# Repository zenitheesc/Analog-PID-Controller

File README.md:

<h1 align="center" style="color:white; background-color:black">Analog PID Controller</h1>
<h4 align="center">
The project was developed in three parts. The first was a simetric supply to 6V at -6V, that was responsable to supply the requires voltages to second part, the PID controler. The PID controller was developed using operational amplifiers in derivatived and integral configuration The tird one was a motor velocity and position sensor, developed using fotodiodes like an encoder.</h4>

<p align="center">

</p>

---

<p align="center">

</p>
<p align = "center">
<a href="zenith.eesc@gmail.com">zenith.eesc@gmail.com</a>
</p>

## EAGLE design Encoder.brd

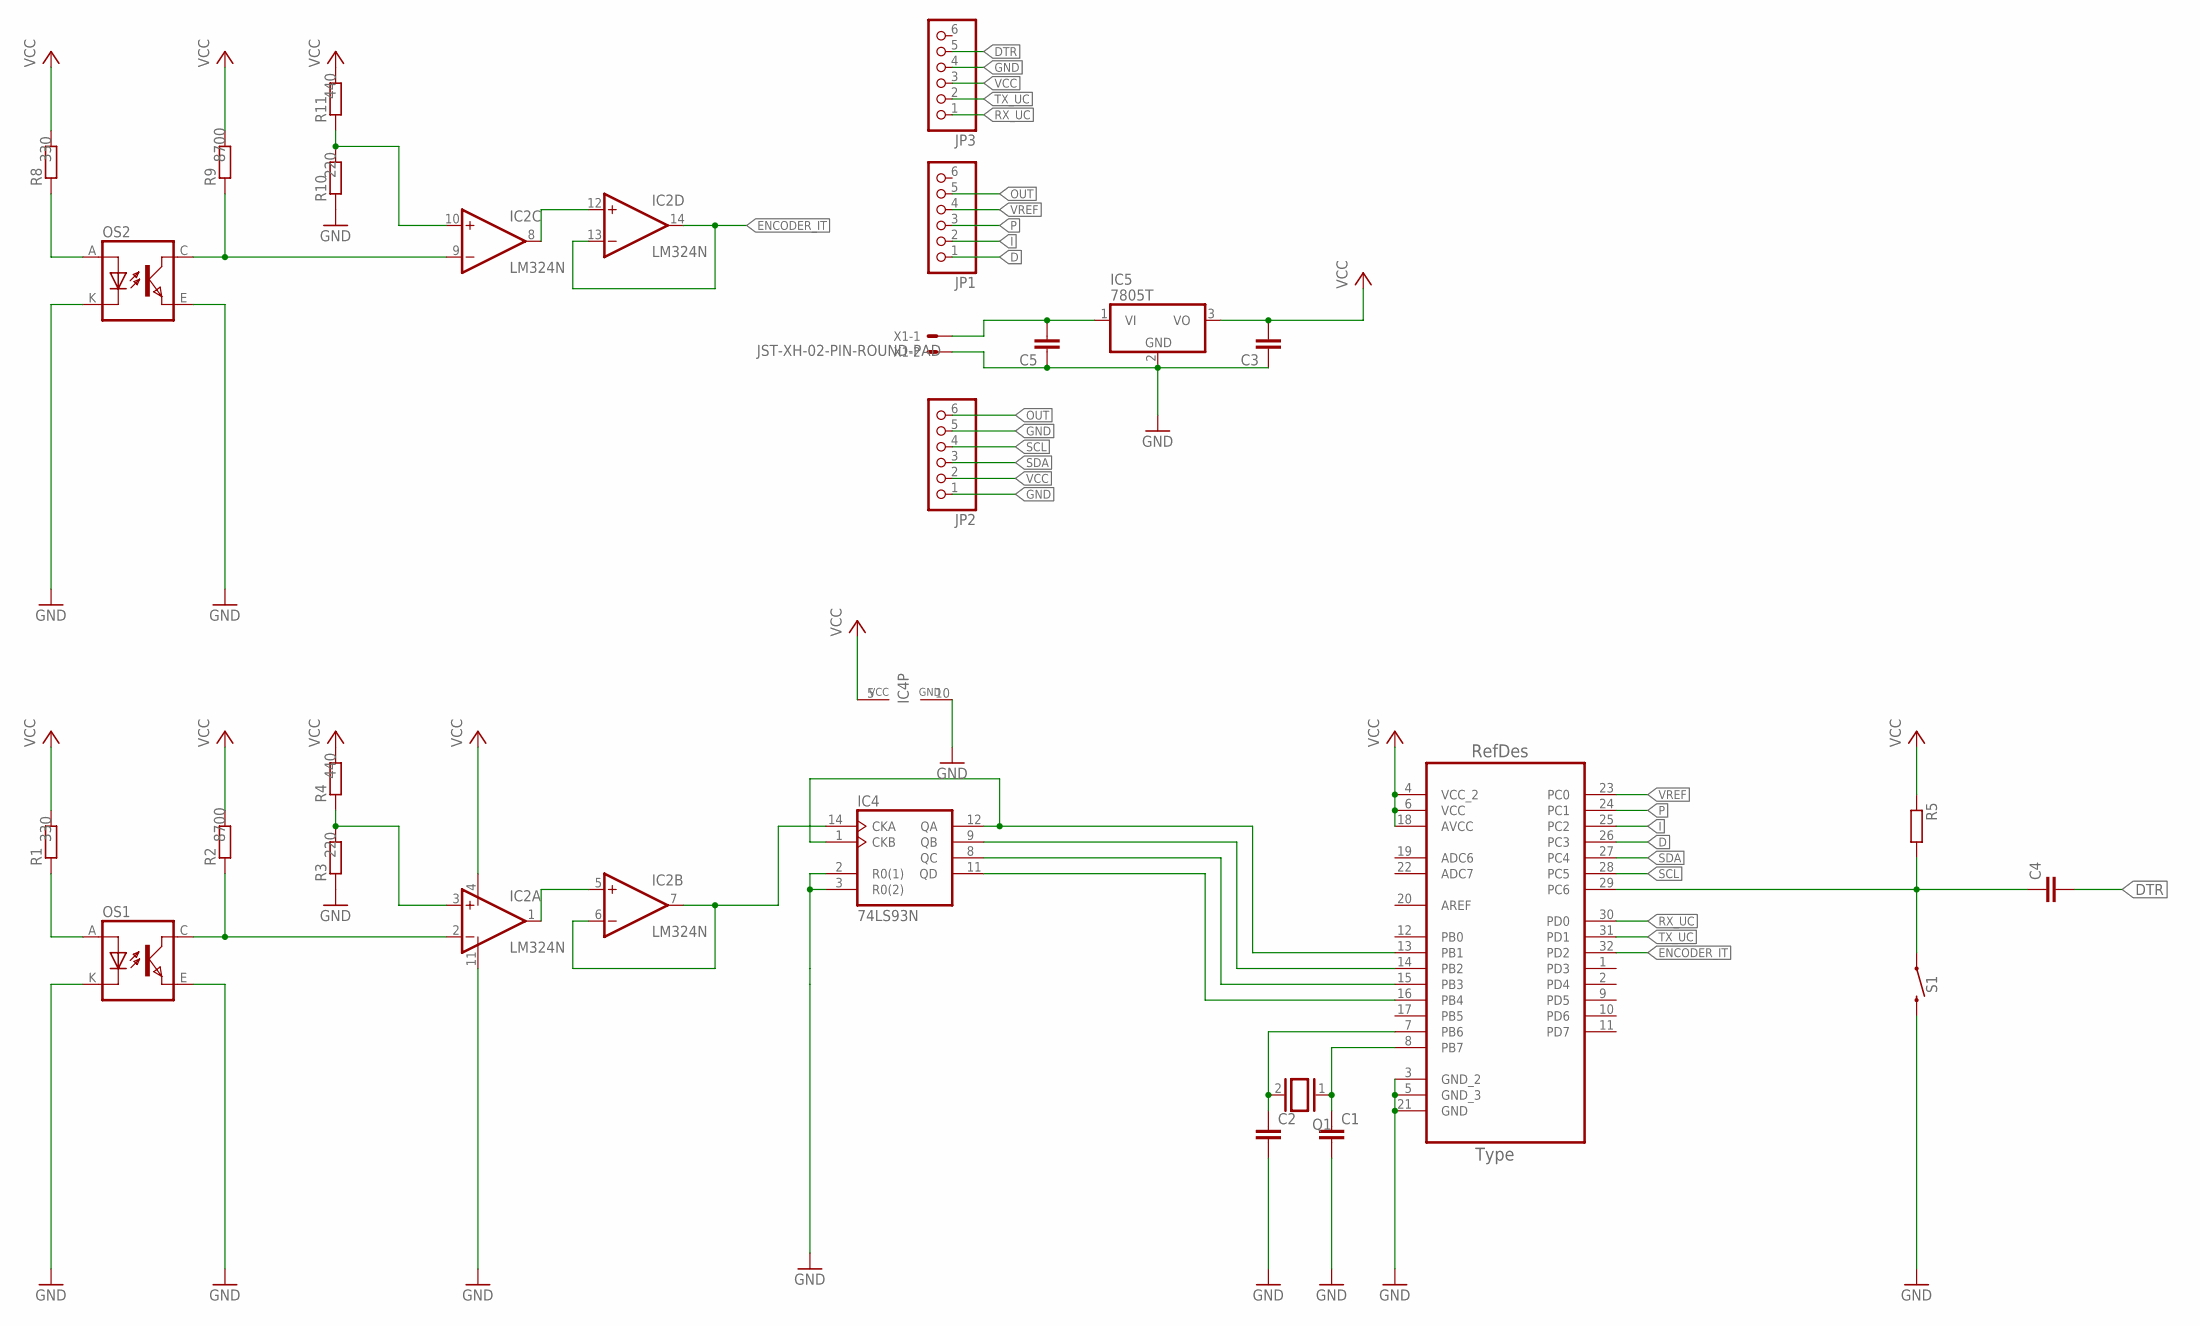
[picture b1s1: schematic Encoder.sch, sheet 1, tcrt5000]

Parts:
C1, C2, C3, C4, C5: C-EUC1206; C1206
IC2: LM324N; DIL14
IC4: 74LS93N; DIL14
IC5: 7805T; TO220H
JP1, JP2, JP3: PINHD-1X6; 1X06
OS1, OS2: TCRT5000
Q1: XTAL/S; QS
R1, R2, R3, R4, R5, R8, R9, R10, R11: R-EU_M1206; M1206
S1: MOMENTARY-SWITCH-SPST-PTH-6.0MM; TACTILE_SWITCH_PTH_6.0MM
U1: ATMEGA328P-AU; QFP80P900X900X120-32N
X1: JST-XH-02-PIN-ROUND-PAD; JST-XH-02-PACKAGE-ROUND-PAD

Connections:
D: JP1.1, U1.26 (PC3)
DTR: C4.2, JP3.5
ENCODER_IT: IC2.13 (-IN), IC2.14 (OUT), U1.32 (PD2)
GND: C1.2, C2.2, C3.1, C5.1, IC2.11 (V-), IC4.2 (R0(1)), IC4.3 (R0(2)), IC4.10 (GND), IC5.2 (GND), JP2.1, JP2.5, JP3.4, OS1.E (EMITTER), OS1.K (CATHODE), OS2.E (EMITTER), OS2.K (CATHODE), R3.1, R10.1, S1.3 (2), U1.3 (GND_2), U1.5 (GND_3), U1.21 (GND), X1.2
I: JP1.2, U1.25 (PC2)
unnamed: OS1.A (ANODE), R1.1
unnamed: IC2.2 (-IN), OS1.C (COLLECTOR), R2.1
unnamed: IC2.3 (+IN), R3.2, R4.1
unnamed: IC2.1 (OUT), IC2.5 (+IN)
unnamed: C1.1, Q1.1, U1.8 (PB7)
unnamed: C5.2, IC5.1 (VI), X1.1
unnamed: C2.1, Q1.2, U1.7 (PB6)
unnamed: C4.1, R5.2, S1.1, U1.29 (PC6)
unnamed: IC2.6 (-IN), IC2.7 (OUT), IC4.14 (CKA)
unnamed: IC4.1 (CKB), IC4.12 (QA), U1.13 (PB1)
unnamed: IC2.8 (OUT), IC2.12 (+IN)
unnamed: IC4.9 (QB), U1.14 (PB2)
unnamed: OS2.A (ANODE), R8.1
unnamed: IC2.9 (-IN), OS2.C (COLLECTOR), R9.1
unnamed: IC2.10 (+IN), R10.2, R11.1
unnamed: IC4.8 (QC), U1.15 (PB3)
unnamed: IC4.11 (QD), U1.16 (PB4)
OUT: JP1.5, JP2.6
P: JP1.3, U1.24 (PC1)
RX_UC: JP3.1, U1.30 (PD0)
SCL: JP2.4, U1.28 (PC5)
SDA: JP2.3, U1.27 (PC4)
TX_UC: JP3.2, U1.31 (PD1)
VCC: C3.2, IC2.4 (V+), IC4.5 (VCC), IC5.3 (VO), JP2.2, JP3.3, R1.2, R2.2, R4.2, R5.1, R8.2, R9.2, R11.2, U1.4 (VCC_2), U1.6 (VCC), U1.18 (AVCC)
VREF: JP1.4, U1.23 (PC0)

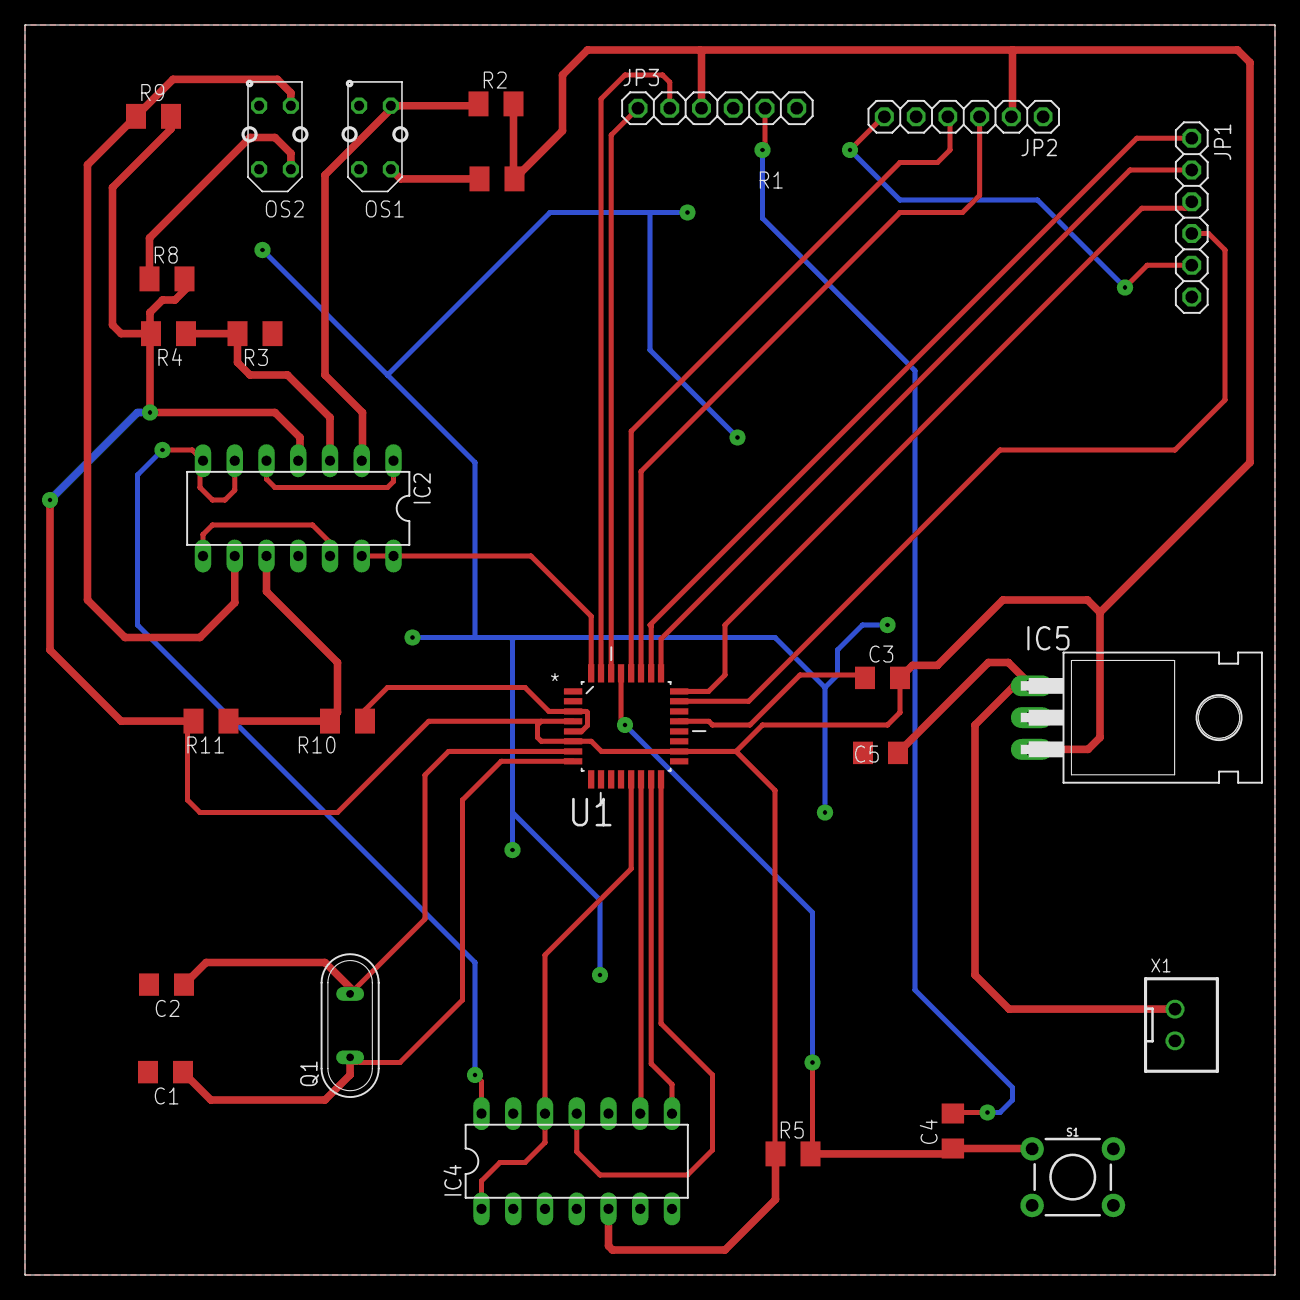
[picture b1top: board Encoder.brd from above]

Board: 2 copper layers, 100.0 x 100.0 mm, 26 parts (0 on the bottom side), 30 nets.

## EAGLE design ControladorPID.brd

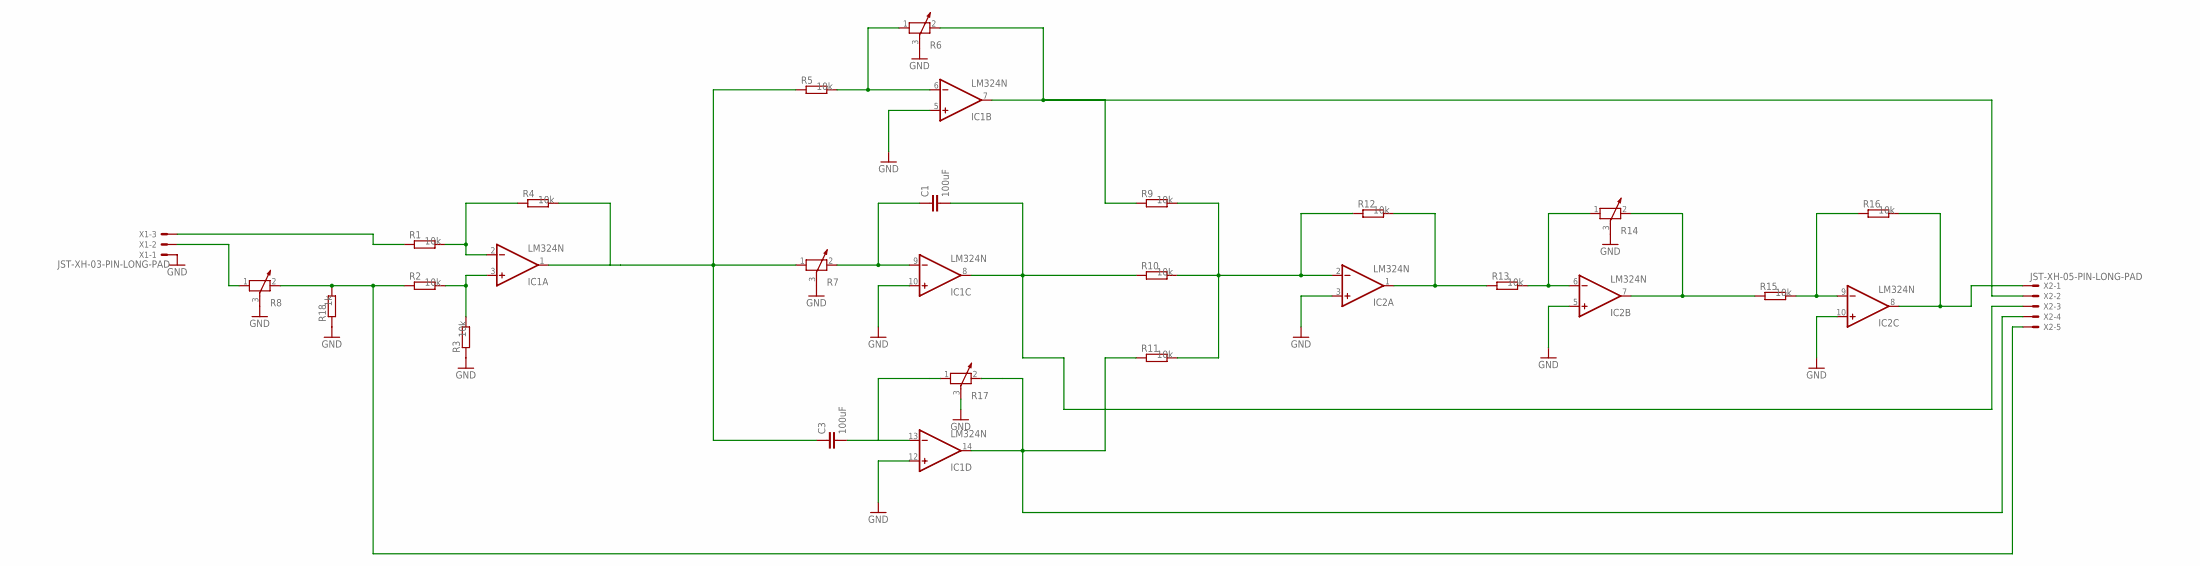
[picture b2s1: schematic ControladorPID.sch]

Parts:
C1, C3: 100uF; C2.5-3
IC1, IC2: LM324N; DIL14
R1, R2, R3, R4, R5, R9, R10, R11, R12, R13, R15, R16, R18: R-EU_M1206; M1206
R6, R7, R8, R14, R17: POTENTIOMETER_PT-10; PT-10
X1: JST-XH-03-PIN-LONG-PAD; JST-XH-03-PACKAGE-LONG-PAD
X2: JST-XH-05-PIN-LONG-PAD; JST-XH-05-PACKAGE-LONG-PAD

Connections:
GND: IC1.5 (+IN), IC1.10 (+IN), IC1.12 (+IN), IC2.3 (+IN), IC2.5 (+IN), IC2.10 (+IN), R3.1, R6.3, R7.3, R8.3, R14.3, R17.3, R18.1, X1.1
unnamed: IC1.2 (-IN), R1.2, R4.1
unnamed: IC1.3 (+IN), R2.2, R3.2
unnamed: C3.1, IC1.1 (OUT), R4.2, R5.1, R7.1
unnamed: C1.2, IC1.8 (OUT), R10.1, X2.3
unnamed: IC1.6 (-IN), R5.2, R6.1
unnamed: R1.1, X1.3
unnamed: C1.1, IC1.9 (-IN), R7.2
unnamed: C3.2, IC1.13 (-IN)
unnamed: IC1.14 (OUT), R11.1, R17.2, X2.4
unnamed: IC2.6 (-IN), R13.2, R14.1
unnamed: IC2.2 (-IN), R9.2, R10.2, R11.2, R12.1
unnamed: IC2.1 (OUT), R12.2, R13.1
unnamed: IC2.7 (OUT), R14.2, R15.1
unnamed: IC2.9 (-IN), R15.2, R16.1
unnamed: IC2.8 (OUT), R16.2, X2.1
unnamed: R2.1, R8.2, R18.2, X2.5
unnamed: R8.1, X1.2
unnamed: IC1.7 (OUT), R6.2, R9.1, X2.2
V+: IC1.4 (V+), IC2.4 (V+)
V-: IC1.11 (V-), IC2.11 (V-)

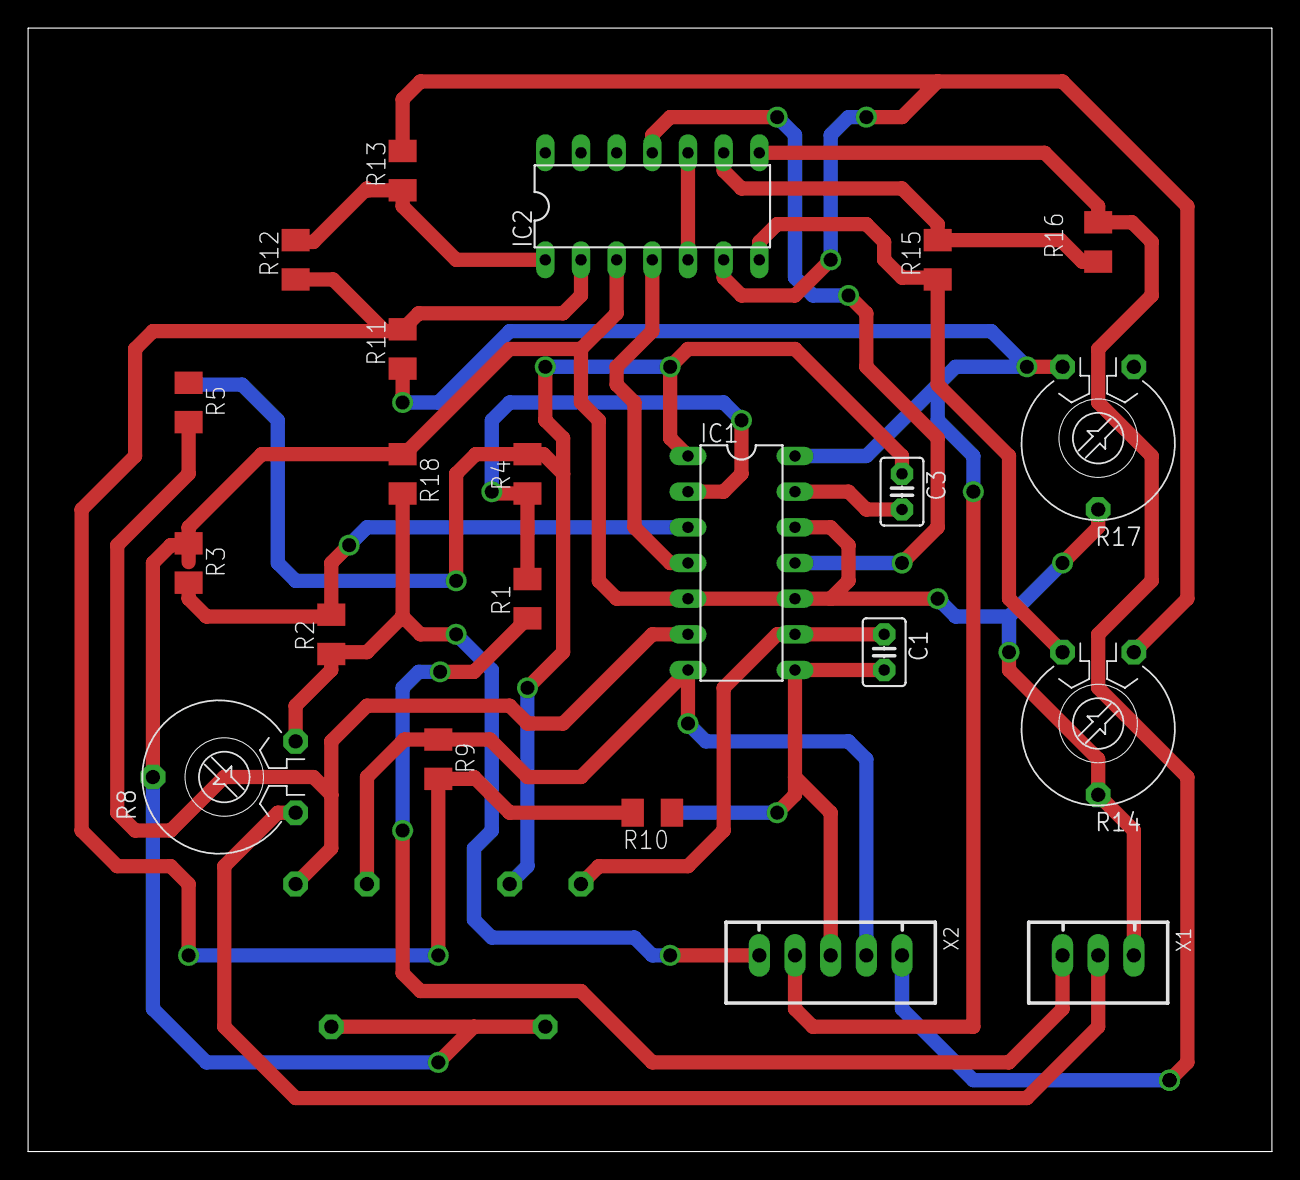
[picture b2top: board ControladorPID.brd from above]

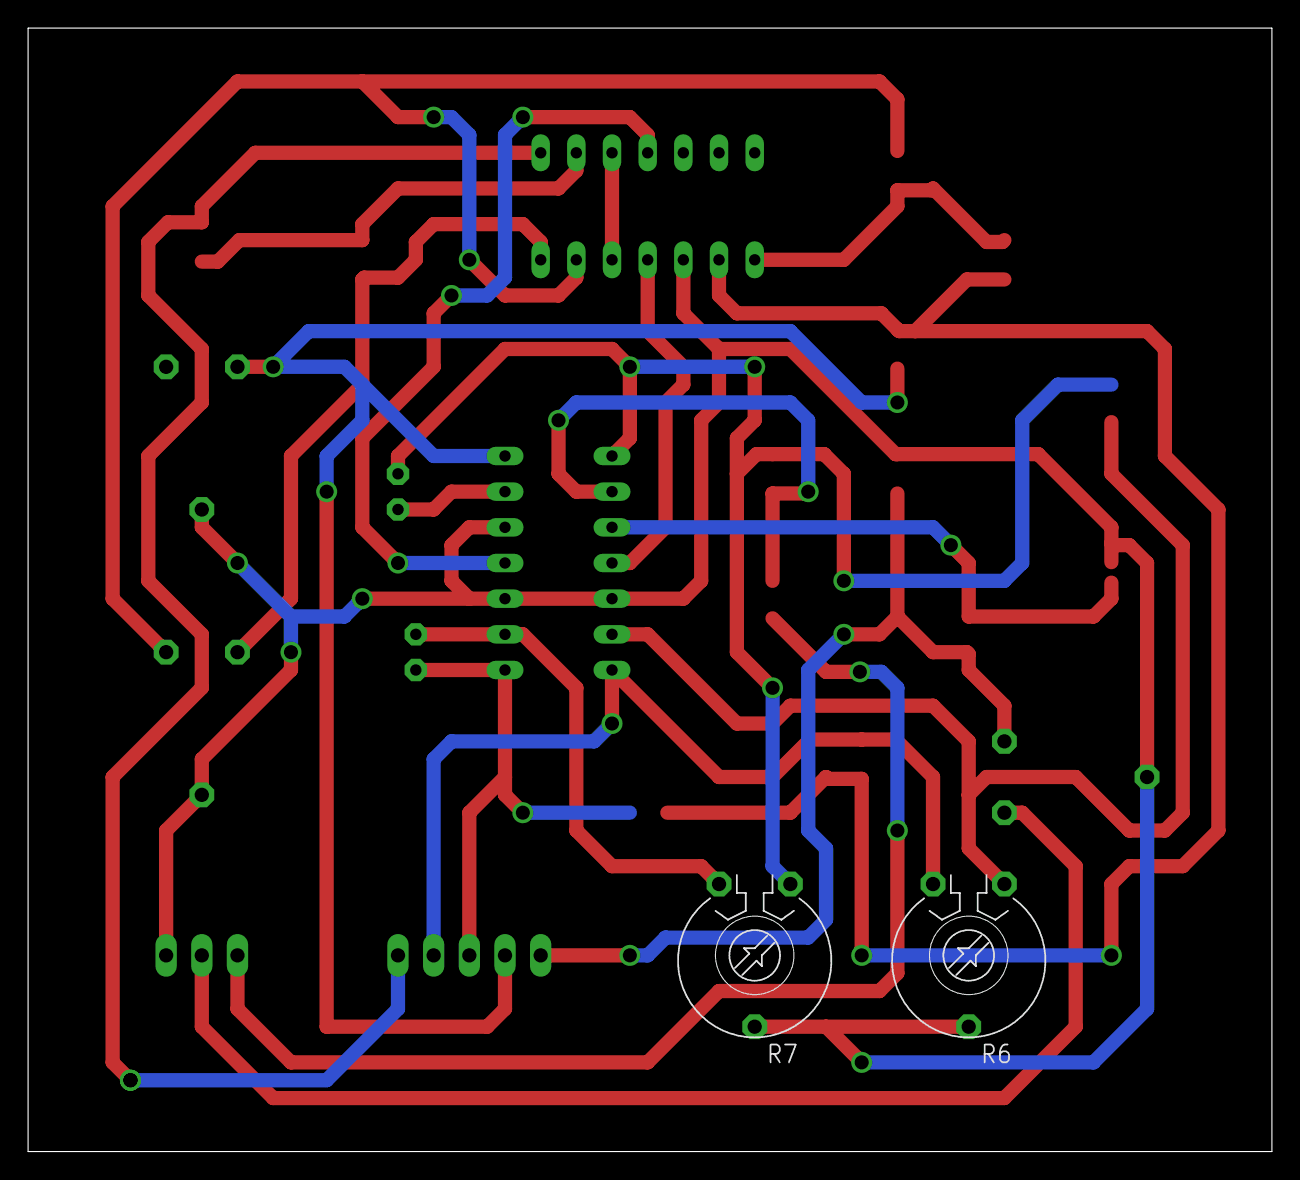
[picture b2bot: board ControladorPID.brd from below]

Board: 2 copper layers, 88.6 x 80.0 mm, 24 parts (2 on the bottom side), 21 nets.

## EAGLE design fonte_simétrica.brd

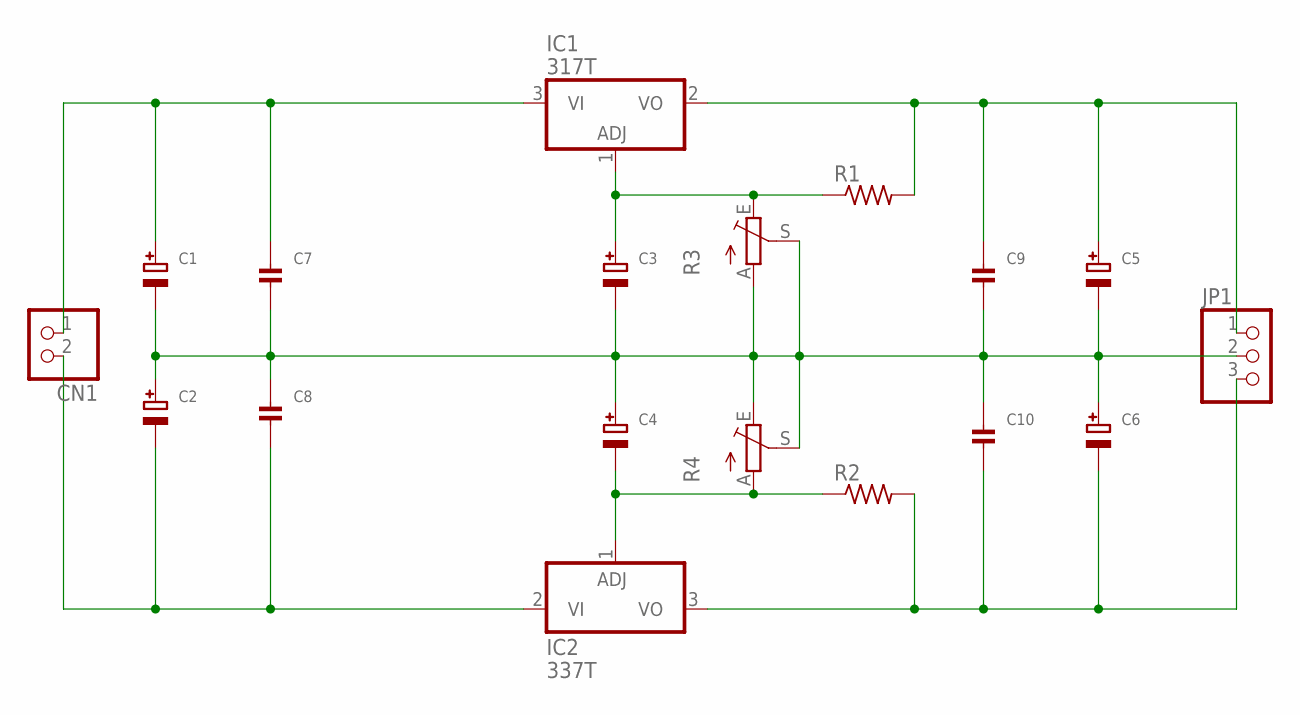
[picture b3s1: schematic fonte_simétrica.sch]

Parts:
C1, C2: CAP_ELECTROLYTICPTH_3.5MMGRID_10MMDIA; CELEC_3.5MM_10MM
C3, C4, C5, C6: CAP_ELECTROLYTICPTH_3.5MMGRID_8MMDIA; CELEC_3.5MM_8MM
C7, C8, C9, C10: CAP_CERAMIC0402; 0402
CN1: JST_2PIN-SMT; JST-PH-2-SMT
IC1: 317T; TO220H
IC2: 337T; TO220H
JP1: PINHD-1X3; 1X03
R1, R2: R-US_0204/7; 0204/7
R3, R4: TRIM_1234-S64YW; S64YW

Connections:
unnamed: C1.+, C7.1, CN1.1 (2), IC1.3 (VI)
unnamed: C1.-, C2.+, C3.-, C4.+, C5.-, C6.+, C7.2, C8.1, C9.2, C10.1, JP1.2, R3.A, R3.S, R4.E, R4.S
unnamed: C6.-, C10.2, IC2.3 (VO), JP1.3, R2.2
unnamed: C2.-, C8.2, CN1.2 (1), IC2.2 (VI)
unnamed: C3.+, IC1.1 (ADJ), R1.1, R3.E
unnamed: C5.+, C9.1, IC1.2 (VO), JP1.1, R1.2
unnamed: C4.-, IC2.1 (ADJ), R2.1, R4.A

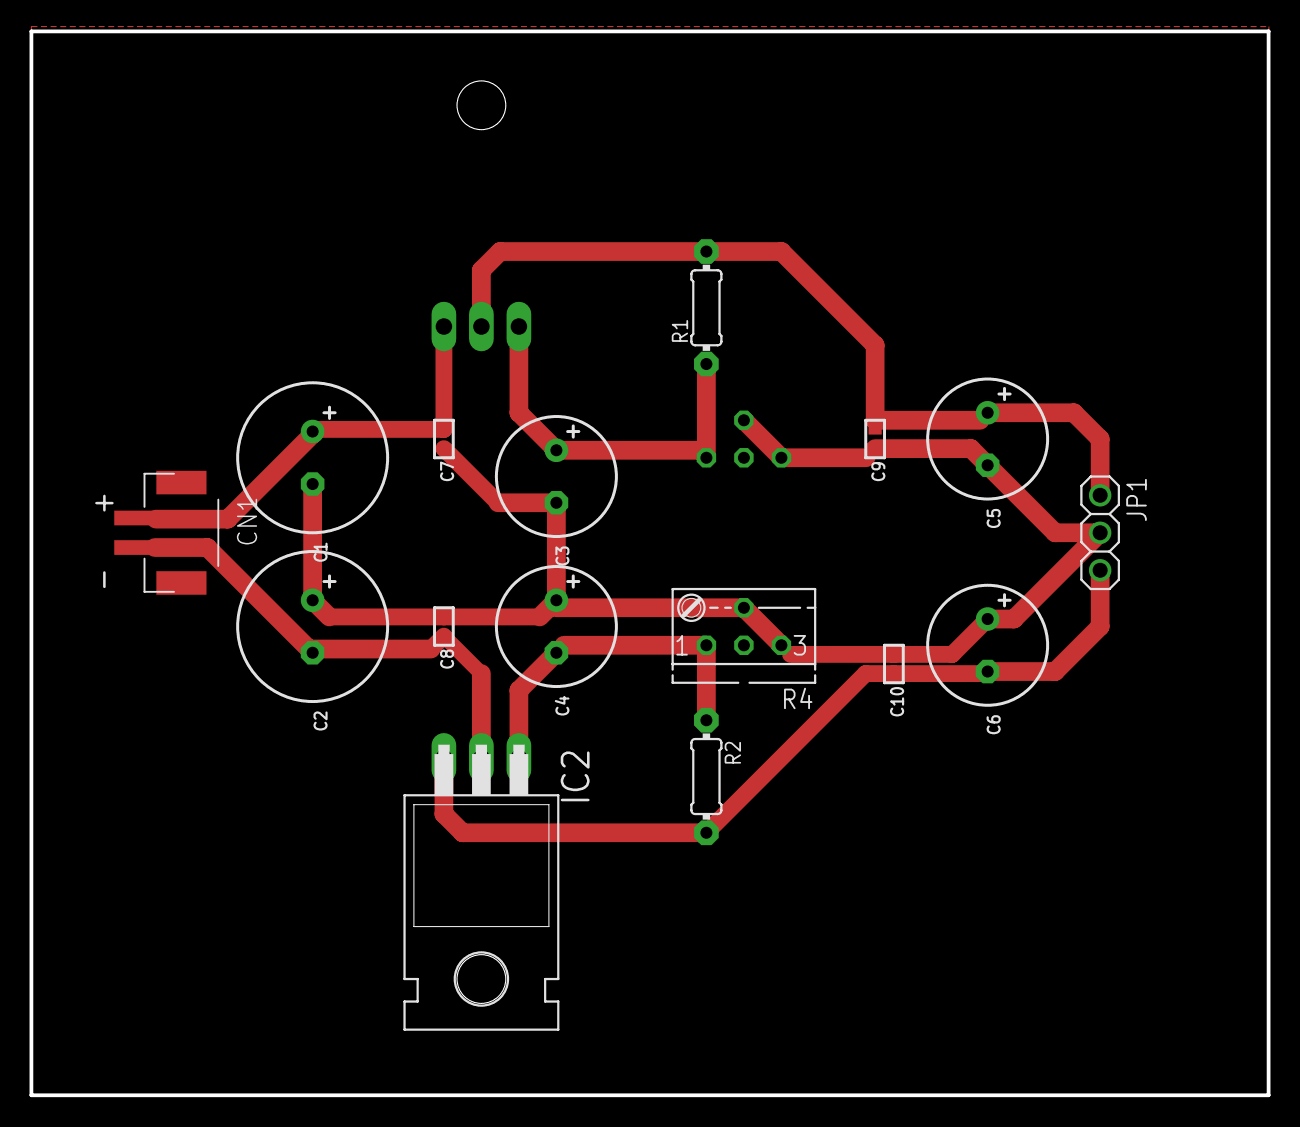
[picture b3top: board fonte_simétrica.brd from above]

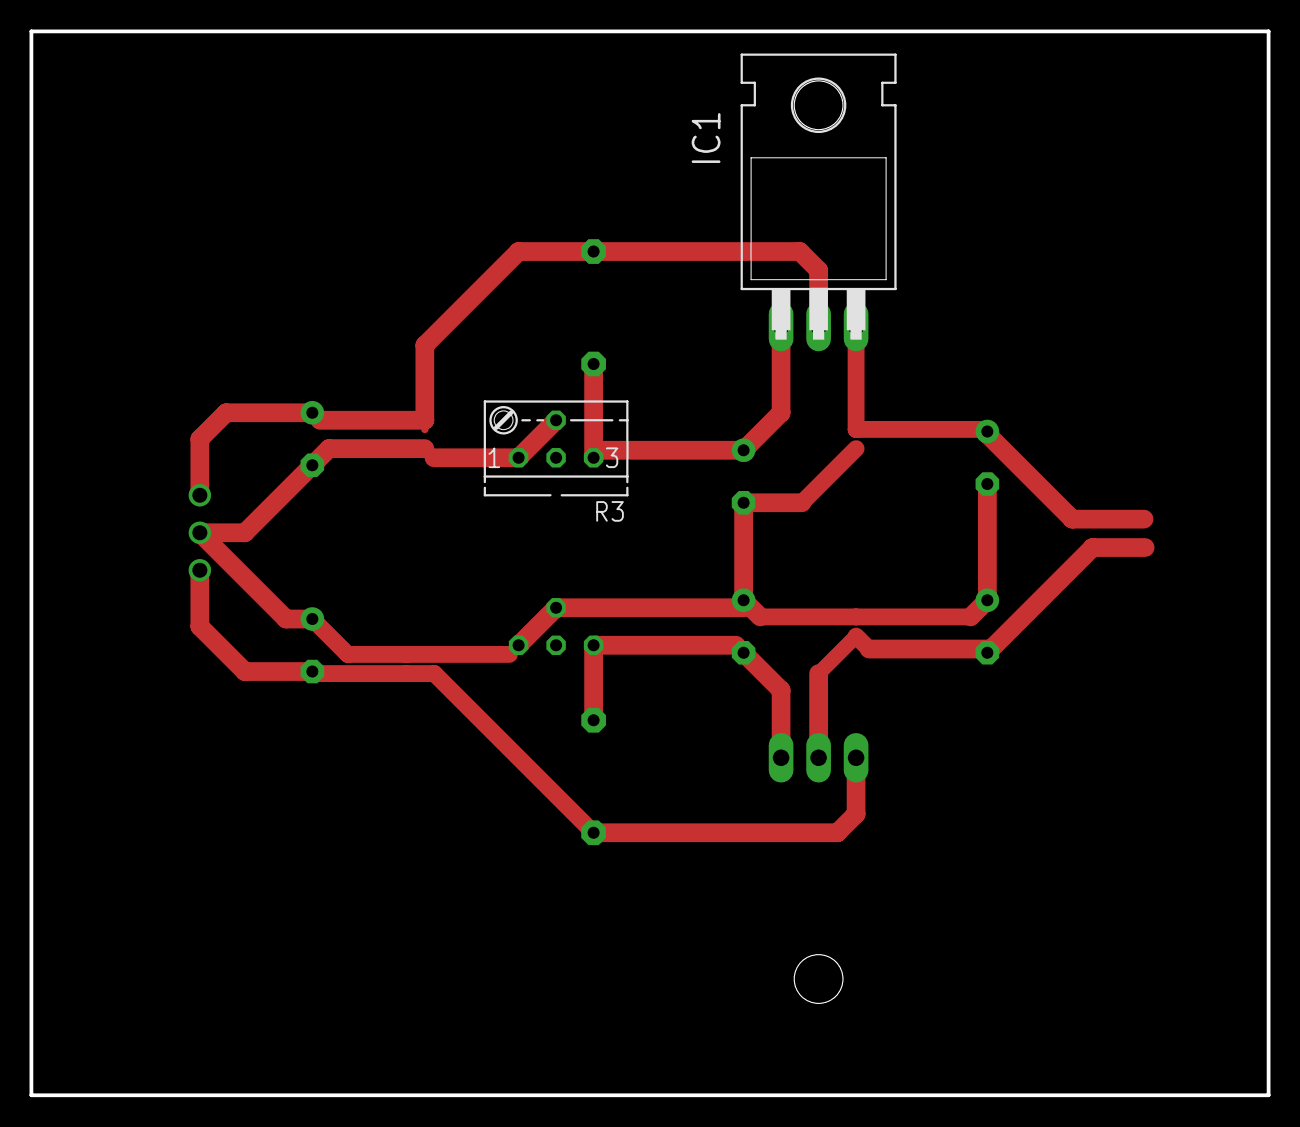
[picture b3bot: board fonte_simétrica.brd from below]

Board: 2 copper layers, 83.8 x 72.1 mm, 18 parts (2 on the bottom side), 7 nets.

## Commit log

2020-06-19 Primeiro
2021-02-28 Testes
2021-02-28 Final Version
2021-02-28 💬 - File Rebuilt | Github Action Runner : 1

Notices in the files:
parts and their libraries:
SparkFun-Switches: Licensing: Creative Commons ShareAlike 4.0 International - https://creativecommons.org/licenses/by-sa/4.0
microbuilder: This work is placed in the public domain, and may be freely used for commercial and non-commercial work with the following conditions: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
